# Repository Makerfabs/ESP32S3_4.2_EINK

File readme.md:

# ESP32 S3 4.2" EINK

```

Version:    V1.0
Author:     Vincent
Create Date:    2024/3/25
Note:

```

[toc]

# Makerfabs

[Makerfabs home page](https://www.makerfabs.com/)

[Makerfabs Wiki](https://wiki.makerfabs.com/)

# ESP32 S3 4.2" EINK
## Intruduce

Product Link ： 

Wiki Link : 

The red and black ink screen uses the ESP32S3 driver, contains an SD card slot and two three-way toggle switches.

## Feature

- Integrated ESP32 S3 2.4G WiFi and Bluetooth
- Input Voltage: 3.7V Battery or 5.0V Type-C
- Resolution: 400 * 300
- Display Color: Red / Black and White

# Code

## Compiler Options

- Use type-c use cable connect USB-TTL to PC.
- Select "ESP32 S3 DEV Module"

Libraries:
- Use 2.0.0   FS
- Use 2.0.0   Wire
- Use 1.0.0   esp32-waveshare-epd
- Use 2.0.0   SD_MMC

We used the ink screen driver provided by Waveshare and modified the pins to fit our hardware.

## Example

### fw_test

Factory firmware.
Refresh the solid color page, display the makerfabs Logo, display simple text and multi-color test, and display TF card capacity, press any key to sleep the screen.

### ebook

Read txt file in tf cards, and use switch to change page.

### pic_display

A bmp picture, binary processing, display on the screen.

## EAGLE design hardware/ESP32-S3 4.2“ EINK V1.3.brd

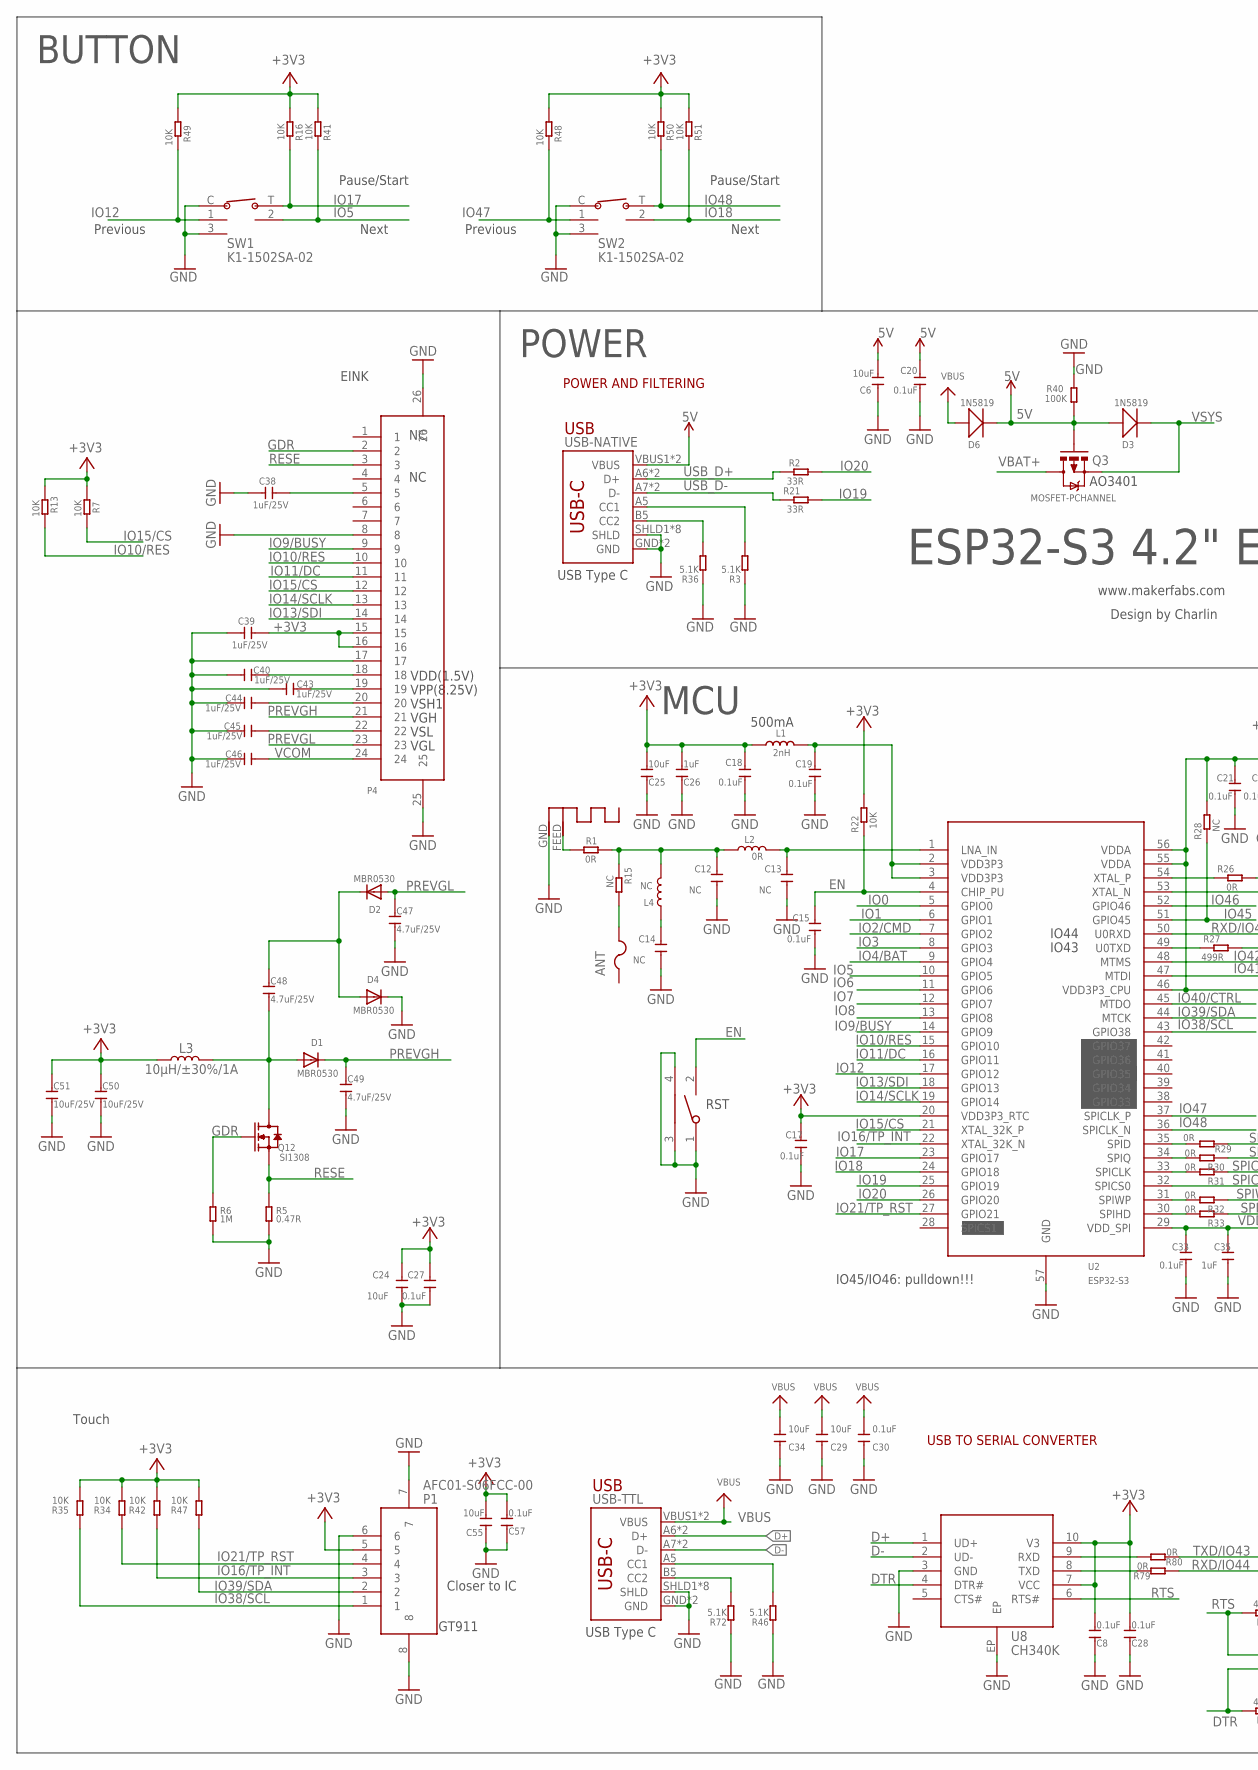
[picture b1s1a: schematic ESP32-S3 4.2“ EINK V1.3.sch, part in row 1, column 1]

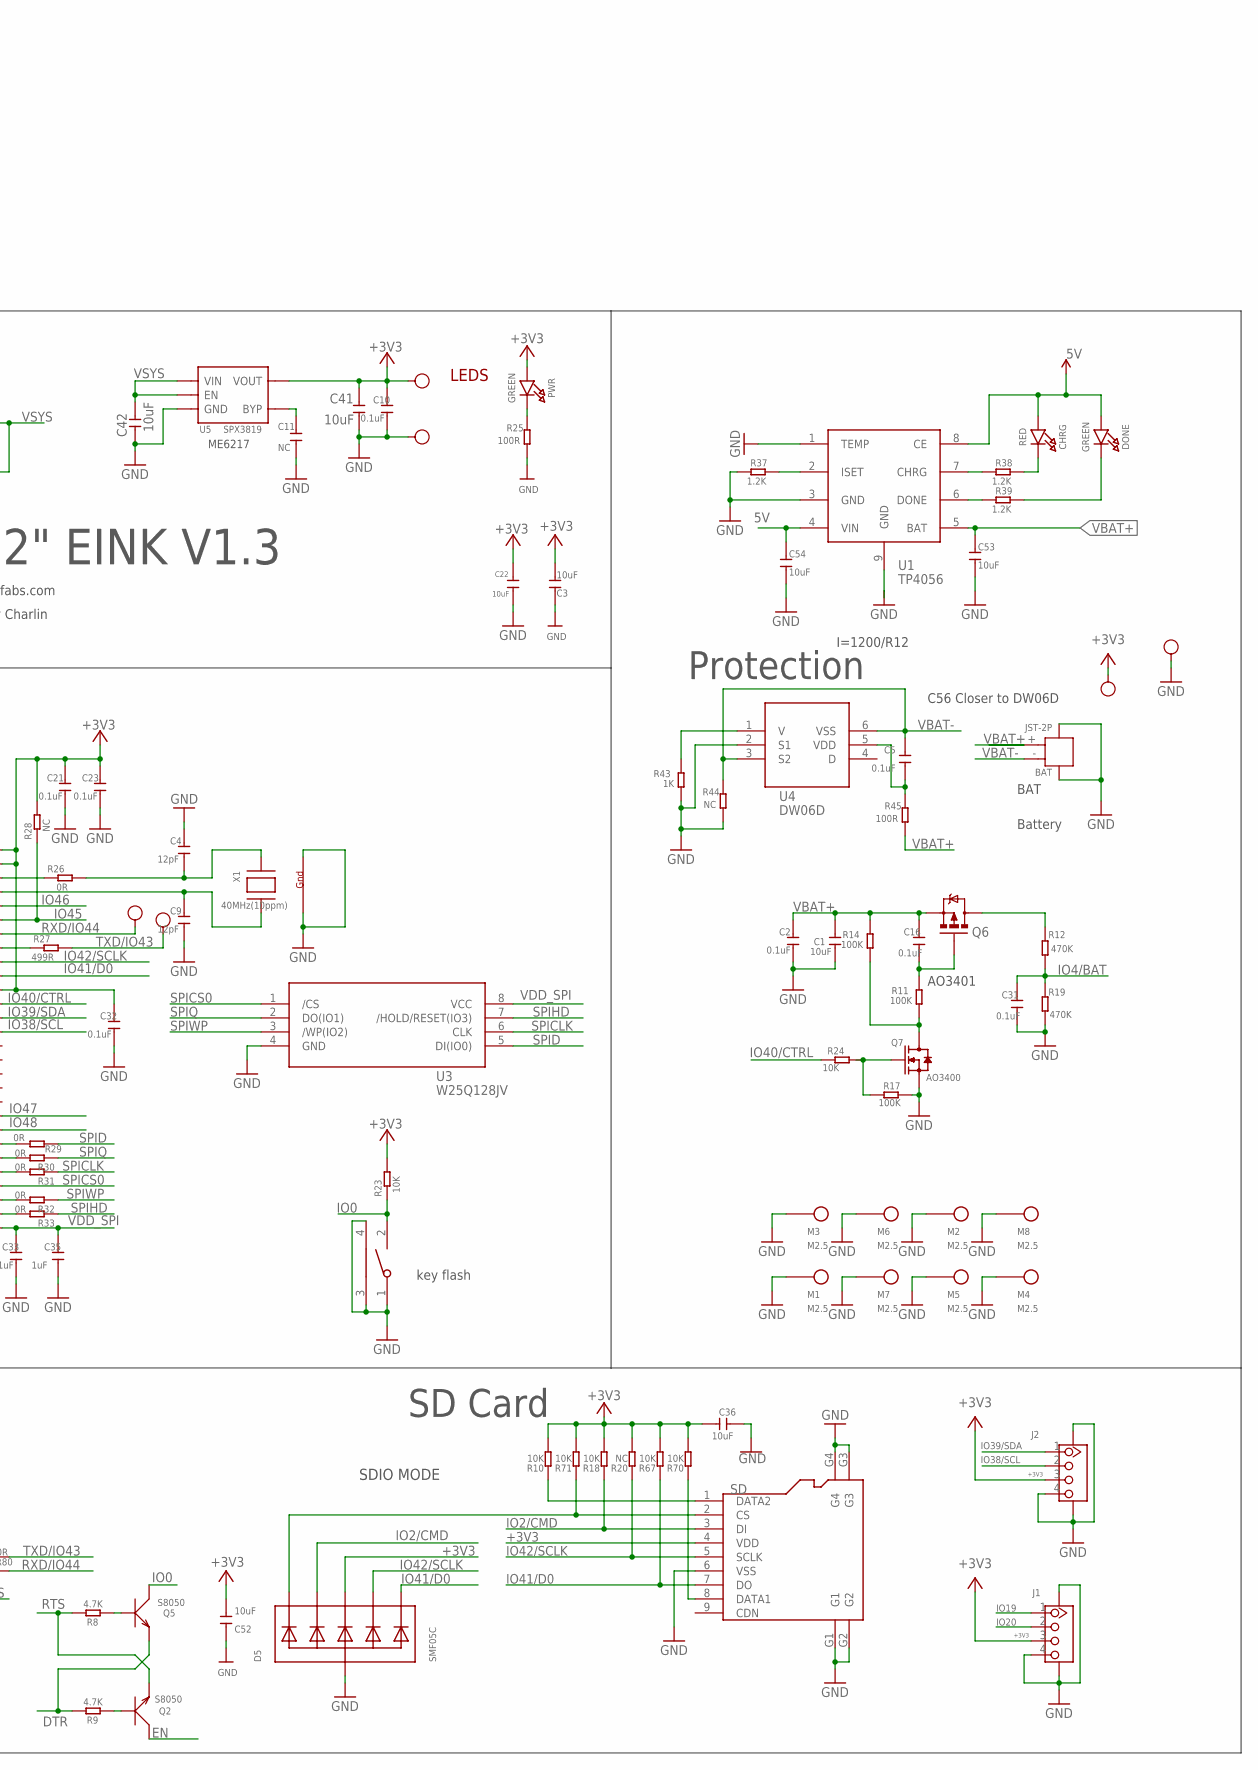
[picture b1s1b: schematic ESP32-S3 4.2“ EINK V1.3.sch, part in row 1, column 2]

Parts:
3V3: TEST-POINT'4545'; TP-D45MIL; PARTNO DNP
ANT: PTCFUSE-1206; R1206
ANT1: ANTENNA; RN-ANT
BAT: JST-2P; HW2-SMD-2.0-90D
C1, C22, C24, C41, C42, C53, C54: 10uF; 0603
C2, C5, C10, C15, C16, C17, C18, C19, C20, C21, C23, C27, C31, C32, C33: 0.1uF; 0603
C3, C6, C25, C29, C34, C36, C52, C55: 10uF; DISCRETE_C0603
C4, C9: 12pF; 0603
C8, C28, C30, C57: 0.1uF; DISCRETE_C0603
C11, C12, C13, C14: NC; 0603
C26: 1uF; DISCRETE_C0603
C35: 1uF; 0603
C38, C39, C40, C43, C44, C45, C46: 1uF/25V; 0603
C47, C48, C49: 4.7uF/25V; 0603
C50, C51: 10uF/25V; 0603
CHRG: RED; CHIPLED_0805_NOOUTLINE
D1, D2, D4: MBR0530; SOD-323F
D3, D6: 1N5819; SOD323
D5: SMF05C; SOT363
DONE: GREEN; CHIPLED_0805_NOOUTLINE
FLASH: TS24CA; 2*4*3.5MM
G: TEST-POINT'4545'; TP-D45MIL; PARTNO DNP
GND: TEST-POINT'4545'; TP-D45MIL; PARTNO DNP
J1, J2: GROVE-CONNECTOR-SMD'90D'; HW4-SMD-2.0-90D
L1: 2nH; DISCRETE_L0603
L2: 0R; 0603
L3: 10µH/±30%/1A; CR54
L4: NC; 0603
M1, M2, M3, M4, M5, M6, M7, M8: M2.5
P1: AFC01-S06FCC-00; SMD8-50P-740L535W
P4: FPC-24P; SMD26-50P-1760L450W
PWR: GREEN; CHIPLED_0805_NOOUTLINE
Q2, Q5: S8050; SOT23
Q3, Q6: MOSFET-PCHANNEL; SOT23-3
Q7: AO3400; DISCRETE_SOT23
Q12: SI1308; SOT23
R1, R26, R29, R30, R31, R32, R33, R79, R80: 0R; R0603
R2, R21: 33R; R0603
R3, R36, R46, R72: 5.1K; DISCRETE_R0603
R5: 0.47R; R0603
R6: 1M; R0603
R7, R13, R16, R22, R23, R24, R41, R48, R49, R50, R51: 10K; R0603
R8, R9: 4.7K; R0603
R10, R18, R34, R35, R42, R47, R67, R70, R71: 10K; DISCRETE_R0603
R11, R14, R17, R40: 100K; R0603
R12, R19: 470K; R0603
R15, R28, R44: NC; R0603
R20: NC; DISCRETE_R0603
R25, R45: 100R; R0603
R27: 499R; R0603
R37, R38, R39: 1.2K; R0603
R43: 1K; R0603
RST: TS24CA; 2*4*3.5MM
RX: TEST-POINT'4545'; TP-D45MIL; PARTNO DNP
SD: HOLDER-MICROSD-9P; 9P-SMD-W/-RING
SW1, SW2: K1-1502SA-02; SMD5-60P-1180L1170W
TX: TEST-POINT'4545'; TP-D45MIL; PARTNO DNP
U1: TP4056; SOP8-1.27P
U2: ESP32-S3; QFN56-7*7MM
U3: W25Q128JV; SOIC-8-208MIL
U4: DW06D; SOT-23-6
U5: SPX3819; SOT23-5
U8: CH340K; ESOP-10-EP-150MIL
USB-NATIVE: USB_C5; USB-C-16P-5
USB-TTL: USB_C5; USB-C-16P-5
V: TEST-POINT'4545'; TP-D45MIL; PARTNO DNP
X1: 40MHz(10ppm); NX3225

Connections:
5V: C6.2, C20.2, C54.1, CHRG.A, D3.+, D6.-, DONE.A, Q3.1 (G), R40.1, U1.4 (VIN), U1.8 (CE), USB-NATIVE.VBUS1 (VBUS), USB-NATIVE.VBUS2 (VBUS)
+3V3: 3V3.T, C3.2, C8.2, C10.2, C17.2, C18.2, C21.2, C22.1, C23.2, C24.2, C25.2, C26.2, C27.2, C28.2, C32.2, C36.2, C39.1, C41.2, C50.1, C51.1, C52.2, C55.2, C57.2, D5.4 (C3), J1.3, J2.3, L1.1, L3.P$1 (1), P1.5, P4.15, P4.16, PWR.A, R7.1, R10.2, R13.1, R16.1, R18.2, R20.2, R22.2, R23.2, R28.2, R34.2, R35.2, R41.1, R42.2, R47.2, R48.1, R49.1, R50.1, R51.1, R67.2, R70.2, R71.2, SD.4 (VDD), U2.20 (VDD3P3_RTC), U2.46 (VDD3P3_CPU), U2.55 (VDDA), U2.56 (VDDA), U5.5 (VOUT), U8.7 (VCC), U8.10 (V3), V.T
D+: U8.1 (UD+), USB-TTL.A6 (D+), USB-TTL.B6 (D+)
D-: U8.2 (UD-), USB-TTL.A7 (D-), USB-TTL.B7 (D-)
DONE: R39.2, U1.6 (DONE)
DTR: Q5.2 (E), R9.2, U8.4 (DTR#)
EN: C15.2, Q2.3 (C), R22.1, RST.2, U2.4 (CHIP_PU)
GDR: P4.2, Q12.1 (G), R6.1
GND: ANT1.GND, BAT.3, BAT.4, C1.1, C2.1, C3.1, C4.2, C6.1, C8.1, C9.1, C10.1, C11.1, C12.1, C13.1, C14.1, C15.1, C17.1, C18.1, C19.1, C20.1, C21.1, C22.2, C23.1, C24.1, C25.1, C26.1, C27.1, C28.1, C29.1, C30.1, C31.1, C32.1, C33.1, C34.1, C35.1, C36.1, C38.2, C39.2, C40.2, C41.1, C42.1, C43.2, C44.2, C45.2, C46.2, C47.2, C49.2, C50.2, C51.2, C52.1, C53.2, C54.2, C55.1, C57.1, D4.C, D5.2 (A), FLASH.1, FLASH.3, FLASH.4, G.T, GND.T, J1.4, J1.SS1, J1.SS2, J2.4, J2.SS1, J2.SS2, M1.1, M2.1, M3.1, M4.1, M5.1, M6.1, M7.1, M8.1, P1.6, P1.7, P1.8, P4.8, P4.17, P4.25, P4.26, Q7.2 (S), R3.1, R5.2, R6.2, R17.1, R19.1, R25.1, R36.1, R37.2, R40.2, R43.1, R44.1, R46.1, R72.1, RST.1, RST.3, RST.4, SD.6 (VSS), SD.G1, SD.G2, SD.G3, SD.G4, SW1.3, SW1.C, SW2.3, SW2.C, U1.1 (TEMP), U1.3 (GND), U1.9 (GND), U2.57 (GND), U3.4 (GND), U4.2 (S1), U5.2 (GND), U8.3 (GND), U8.EP, USB-NATIVE.GND, USB-NATIVE.GND2 (GND), USB-NATIVE.SHLD1 (SHLD), USB-NATIVE.SHLD2 (SHLD), USB-NATIVE.SHLD3 (SHLD), USB-NATIVE.SHLD4 (SHLD), USB-NATIVE.SHLD5 (SHLD), USB-NATIVE.SHLD6 (SHLD), USB-NATIVE.SHLD7 (SHLD), USB-NATIVE.SHLD8 (SHLD), USB-TTL.GND, USB-TTL.GND2 (GND), USB-TTL.SHLD1 (SHLD), USB-TTL.SHLD2 (SHLD), USB-TTL.SHLD3 (SHLD), USB-TTL.SHLD4 (SHLD), USB-TTL.SHLD5 (SHLD), USB-TTL.SHLD6 (SHLD), USB-TTL.SHLD7 (SHLD), USB-TTL.SHLD8 (SHLD), X1.2 (G2), X1.4 (G1)
IO0: FLASH.2, Q5.3 (C), R23.1, U2.5 (GPIO0)
IO1: U2.6 (GPIO1)
IO2/CMD: D5.3 (C2), R18.1, SD.3 (DI), U2.7 (GPIO2)
IO3: U2.8 (GPIO3)
IO4/BAT: C31.2, R12.1, R19.2, U2.9 (GPIO4)
IO5: R41.2, SW1.2, U2.10 (GPIO5)
IO6: U2.11 (GPIO6)
IO7: U2.12 (GPIO7)
IO8: U2.13 (GPIO8)
IO9/BUSY: P4.9, U2.14 (GPIO9)
IO10/RES: P4.10, R13.2, U2.15 (GPIO10)
IO11/DC: P4.11, U2.16 (GPIO11)
IO12: R49.2, SW1.1, U2.17 (GPIO12)
IO13/SDI: P4.14, U2.18 (GPIO13)
IO14/SCLK: P4.13, U2.19 (GPIO14)
IO15/CS: P4.12, R7.2, U2.21 (XTAL_32K_P)
IO16/TP_INT: P1.3, R42.1, U2.22 (XTAL_32K_N)
IO17: R16.2, SW1.T, U2.23 (GPIO17)
IO18: R51.2, SW2.2, U2.24 (GPIO18)
IO19: J1.1, R21.2, U2.25 (GPIO19)
IO20: J1.2, R2.2, U2.26 (GPIO20)
IO21/TP_RST: P1.4, R34.1, U2.27 (GPIO21)
IO38/SCL: J2.2, P1.1, R35.1, U2.43 (GPIO38)
IO39/SDA: J2.1, P1.2, R47.1, U2.44 (MTCK)
IO40/CTRL: R24.2, U2.45 (MTDO)
IO41/D0: D5.6 (C5), R67.1, SD.7 (DO), U2.47 (MTDI)
IO42/SCLK: D5.5 (C4), R20.1, SD.5 (SCLK), U2.48 (MTMS)
IO45: R28.1, U2.51 (GPIO45)
IO46: U2.52 (GPIO46)
IO47: R48.2, SW2.1, U2.37 (SPICLK_P)
IO48: R50.2, SW2.T, U2.36 (SPICLK_N)
ISET: R37.1, U1.2 (ISET)
unnamed: C38.1, P4.5
unnamed: ANT1.FEED, R1.1
unnamed: C16.1, Q6.1 (G), R11.2
unnamed: C43.1, P4.19
unnamed: C44.1, P4.20
unnamed: R3.2, USB-NATIVE.A5 (CC1)
unnamed: PWR.C, R25.2
unnamed: Q2.1 (B), R9.1
unnamed: C45.1, P4.22
unnamed: Q6.3 (D), R12.2
unnamed: C48.1, D2.C, D4.A
unnamed: Q5.1 (B), R8.1
unnamed: R79.2, U8.8 (TXD)
unnamed: R36.2, USB-NATIVE.B5 (CC2)
unnamed: Q7.3 (D), R11.1, R14.1
unnamed: R10.1, SD.1 (DATA2)
unnamed: R46.2, USB-TTL.A5 (CC1)
unnamed: R72.2, USB-TTL.B5 (CC2)
unnamed: Q7.1 (G), R17.2, R24.1
unnamed: R70.1, SD.8 (DATA1)
unnamed: C40.1, P4.18
unnamed: DONE.C, R39.1
unnamed: R38.2, U1.7 (CHRG)
unnamed: ANT.2, R15.2
unnamed: D5.1 (C1), R71.1, SD.2 (CS)
unnamed: CHRG.C, R38.1
unnamed: C5.1, R45.2, U4.5 (VDD)
unnamed: R43.2, U4.1 (V)
unnamed: C12.2, L2.1, L4.2, R1.2, R15.1
unnamed: C13.2, L2.2, U2.1 (LNA_IN)
unnamed: R29.2, U2.35 (SPID)
unnamed: C19.2, L1.2, U2.2 (VDD3P3), U2.3 (VDD3P3)
unnamed: C14.2, L4.1
unnamed: R30.2, U2.34 (SPIQ)
unnamed: R80.2, U8.9 (RXD)
unnamed: R26.1, U2.54 (XTAL_P)
unnamed: R31.2, U2.33 (SPICLK)
unnamed: R32.2, U2.31 (SPIWP)
unnamed: R33.2, U2.30 (SPIHD)
unnamed: R27.1, U2.49 (U0TXD)
unnamed: C9.2, U2.53 (XTAL_N), X1.3 (X2)
unnamed: C4.1, R26.2, X1.1 (X1)
unnamed: C48.2, D1.A, L3.P$2 (2), Q12.3 (D)
unnamed: C11.2, U5.4 (BYP)
PREVGH: C49.1, D1.C, P4.21
PREVGL: C47.1, D2.A, P4.23
RESE: P4.3, Q12.2 (S), R5.1
RTS: Q2.2 (E), R8.2, U8.6 (RTS#)
RXD/IO44: R79.1, RX.T, U2.50 (U0RXD)
SPICLK: R31.1, U3.6 (CLK)
SPICS0: U2.32 (SPICS0), U3.1 (/CS)
SPID: R29.1, U3.5 (DI(IO0))
SPIHD: R33.1, U3.7 (/HOLD/RESET(IO3))
SPIQ: R30.1, U3.2 (DO(IO1))
SPIWP: R32.1, U3.3 (/WP(IO2))
TXD/IO43: R27.2, R80.1, TX.T
USB_D+: R2.1, USB-NATIVE.A6 (D+), USB-NATIVE.B6 (D+)
USB_D-: R21.1, USB-NATIVE.A7 (D-), USB-NATIVE.B7 (D-)
VBAT+: BAT.+ (1), C1.2, C2.2, C16.2, C53.1, Q3.3 (D), Q6.2 (S), R14.2, R45.1, U1.5 (BAT)
VBAT-: BAT.- (2), C5.2, R44.2, U4.3 (S2), U4.6 (VSS)
VBUS: C29.2, C30.2, C34.2, D6.+, USB-TTL.VBUS1 (VBUS), USB-TTL.VBUS2 (VBUS)
VCOM: C46.1, P4.24
VDD_SPI: C33.2, C35.2, U2.29 (VDD_SPI), U3.8 (VCC)
VSYS: C42.2, D3.-, Q3.2 (S), U5.1 (VIN), U5.3 (EN)

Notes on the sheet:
www.makerfabs.com
Design by Charlin
LEDS
POWER AND FILTERING
key flash
POWER
USB
USB Type C
MCU
500mA
ME6217
AO3401
IO45/IO46: pulldown!!!
IO43
IO44
RST
ESP32-S3 4.2" EINK V1.3
EINK
VDD(1.5V)
VPP(8.25V)
VSH1
VGH
VSL
VGL
USB TO SERIAL CONVERTER
SD Card
SDIO MODE
I=1200/R12
Battery
C56 Closer to DW06D
Protection
BAT
GT911
Closer to IC
Touch
Previous
Next
Pause/Start
BUTTON

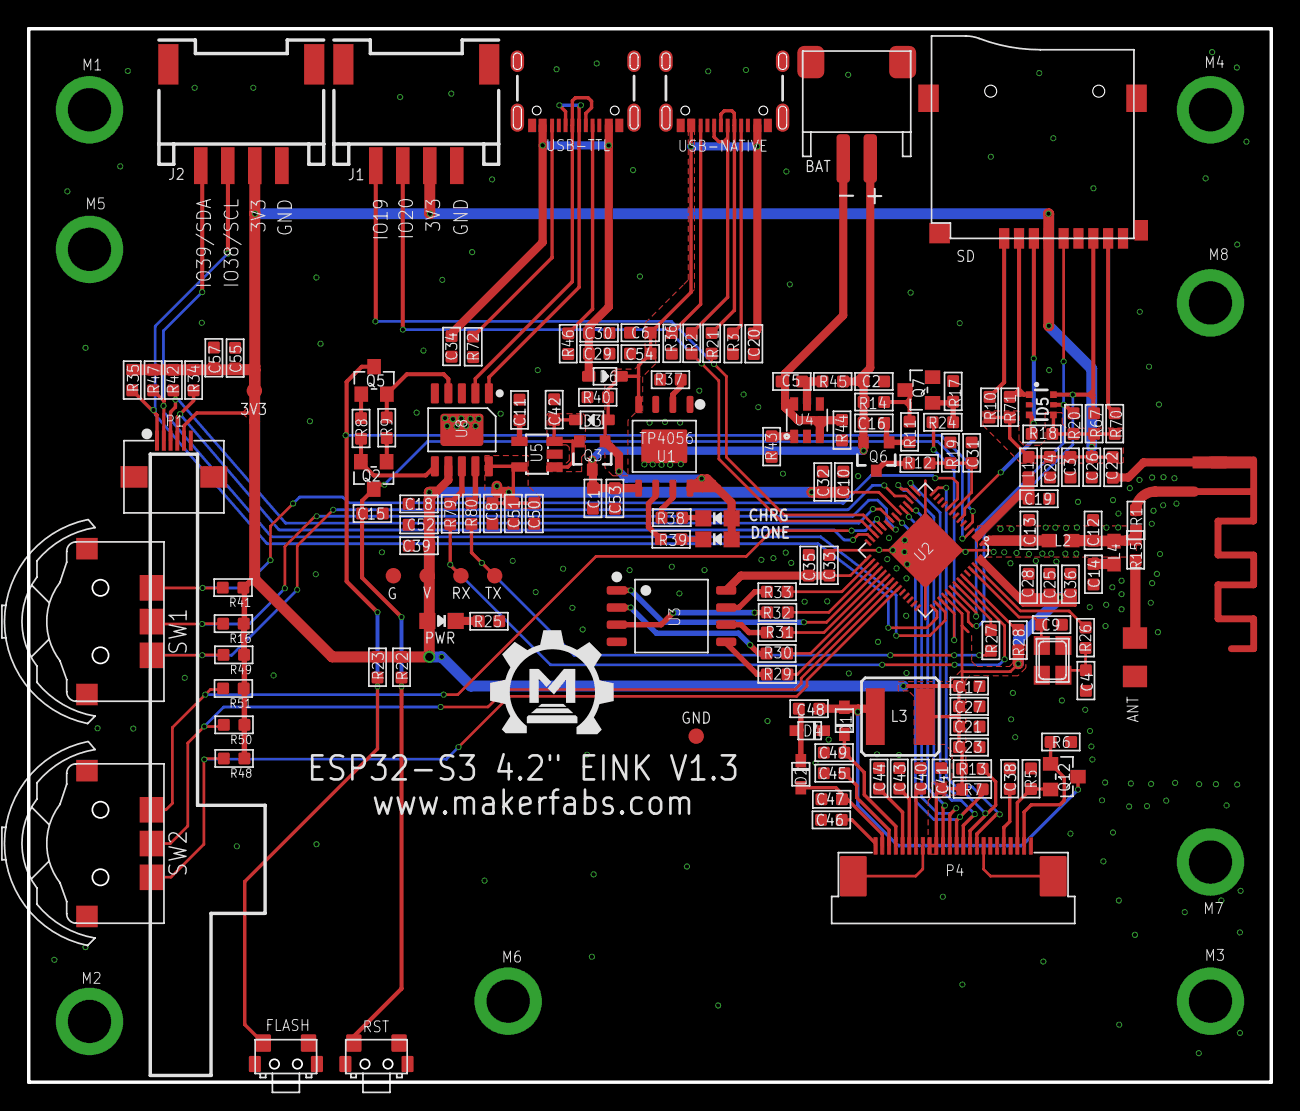
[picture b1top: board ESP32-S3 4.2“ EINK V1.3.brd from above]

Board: 2 copper layers, 92.0 x 78.0 mm, 165 parts (0 on the bottom side), 99 nets.

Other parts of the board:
U$1: MAKERFABS_0.3

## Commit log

2024-03-25 Create project
2024-03-28 Create hardware
2024-03-28 Create 1
2024-03-28 Create image2lcd
2024-03-28 Create q
2024-04-18 Add demo
2024-06-07 at_demo
2024-06-08 rmdir

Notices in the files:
parts and their libraries:
microbuilder: This work is placed in the public domain, and may be freely used for commercial and non-commercial work with the following conditions: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
User-Submitted: Licensing: Creative Commons ShareAlike 4.0 International - https://creativecommons.org/licenses/by-sa/4.0
